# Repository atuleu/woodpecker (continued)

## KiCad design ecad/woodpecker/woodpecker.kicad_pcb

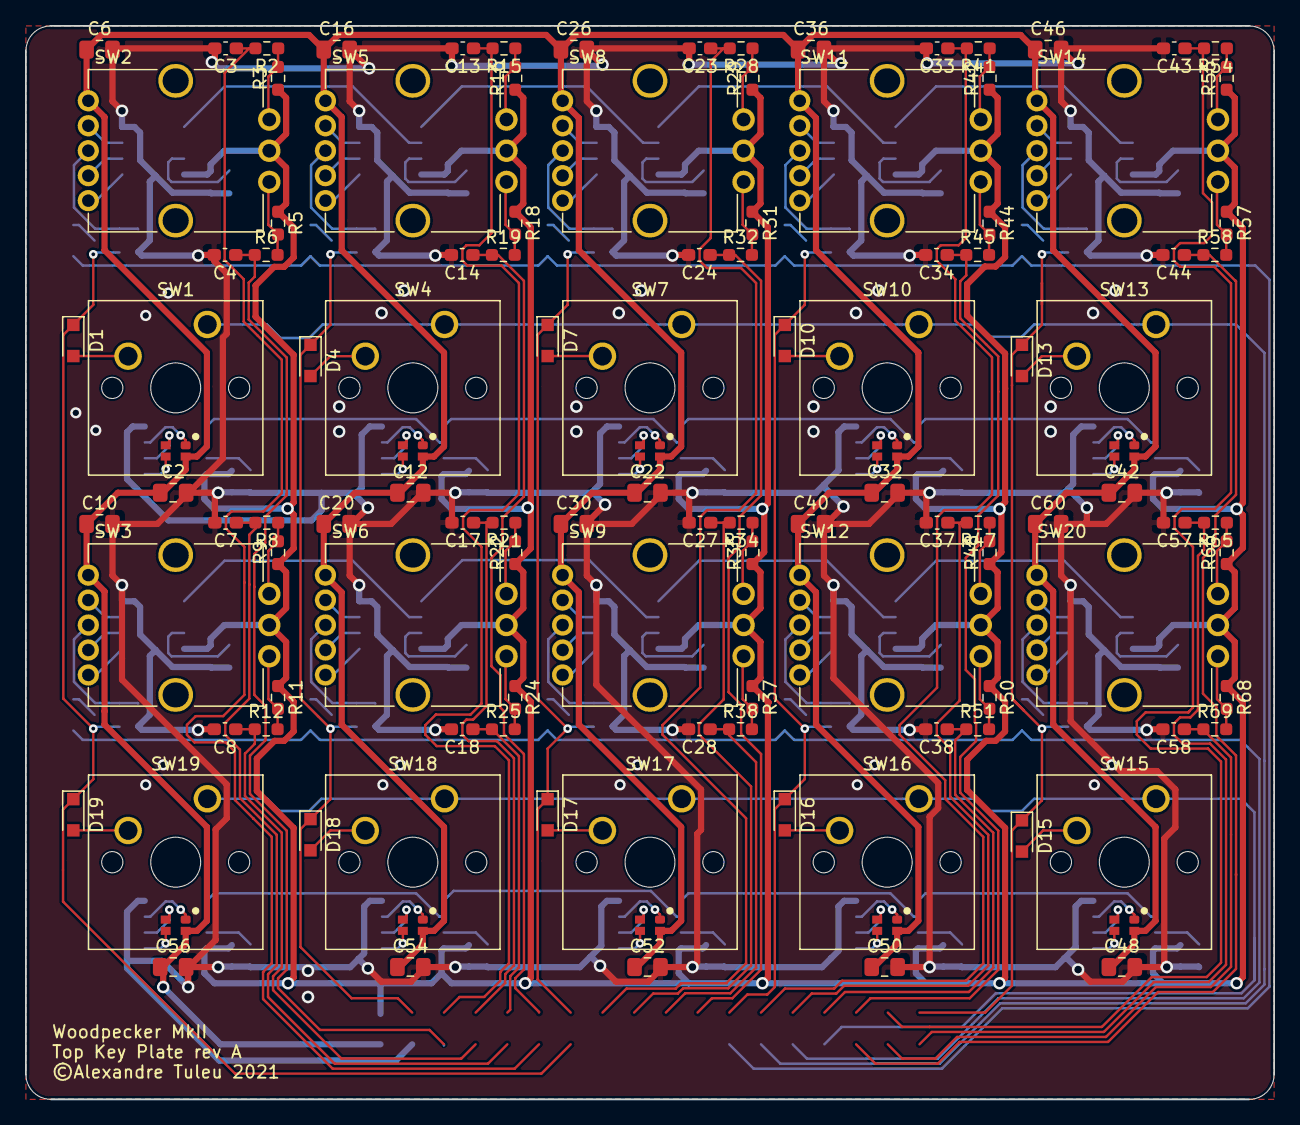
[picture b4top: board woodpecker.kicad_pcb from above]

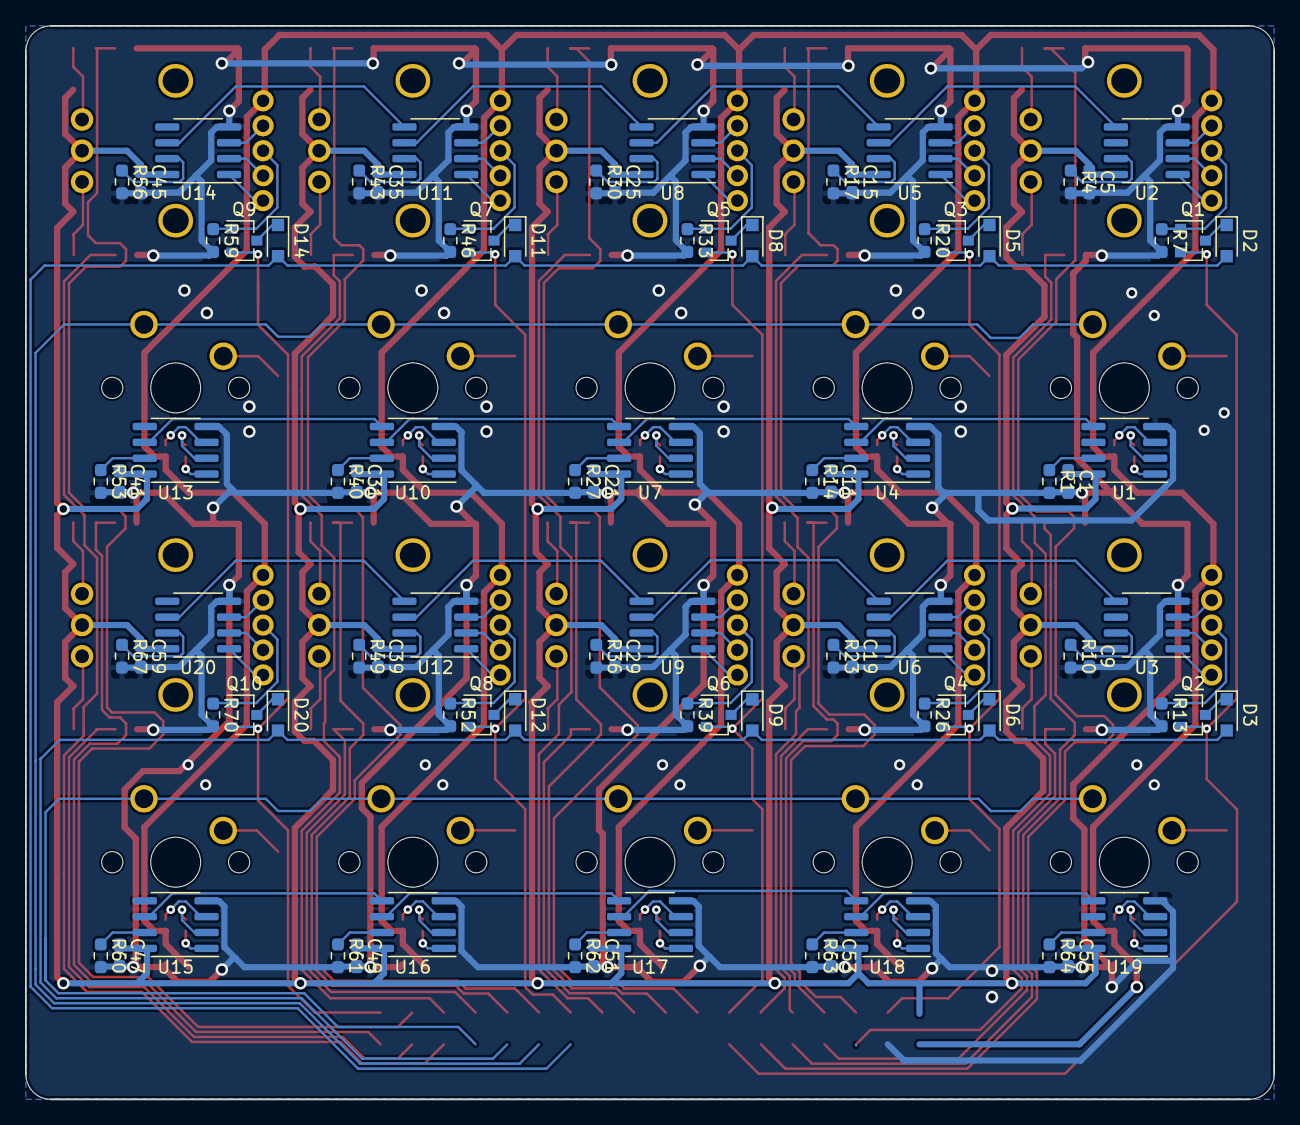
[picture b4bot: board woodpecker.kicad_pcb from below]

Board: 2 copper layers, 100.0 x 86.0 mm, 200 parts (90 on the bottom side), 178 nets.

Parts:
C1, C5, C9, C11, C15, C19, C21, C25, C29, C31, C35, C39, C41, C45, C47, C49, C51, C53, C55, C59: 100nF; C_0603_1608Metric_Pad1.08x0.95mm_HandSolder
C2, C6, C10, C12, C16, C20, C22, C26, C30, C32, C36, C40, C42, C46, C48, C50, C52, C54, C56, C60: 2.2uF; C_0805_2012Metric_Pad1.18x1.45mm_HandSolder
C3, C4, C7, C8, C13, C14, C17, C18, C23, C24, C27, C28, C33, C34, C37, C38, C43, C44, C57, C58: 10nF; C_0603_1608Metric_Pad1.08x0.95mm_HandSolder
D1, D2, D3, D4, D5, D6, D7, D8, D9, D10, D11, D12, D13, D14, D15, D16, D17, D18, D19, D20: 1N4148WS; D_SOD-323_HandSoldering
Q1, Q2, Q3, Q4, Q5, Q6, Q7, Q8, Q9, Q10: BSS138; SOT-23
R1, R4, R10, R14, R17, R23, R27, R30, R36, R40, R43, R49, R53, R56, R60, R61, R62, R63, R64, R67: 10.5K; R_0603_1608Metric_Pad0.98x0.95mm_HandSolder
R2, R3, R5, R6, R7, R8, R9, R11, R12, R13, R15, R16, R18, R19, R20, R21, R22, R24, R25, R26, R28, R29, R31, R32, R33, R34, R35, R37, R38, R39, R41, R42, R44, R45, R46, R47, R48, R50, R51, R52, R54, R55, R57, R58, R59, R65, R66, R68, R69, R70: 10K; R_0603_1608Metric_Pad0.98x0.95mm_HandSolder
SW1, SW4, SW7, SW10, SW13, SW15, SW16, SW17, SW18, SW19: Cherry_MX_LED; SW_Cherry_MX_1.00u_PCB_SMD_LED
SW2, SW3, SW5, SW6, SW8, SW9, SW11, SW12, SW14, SW20: PEL12T; PEL12T-4xxxS-S1024
U1, U2, U3, U4, U5, U6, U7, U8, U9, U10, U11, U12, U13, U14, U15, U16, U17, U18, U19, U20: TLC5973; SOIC-8_3.9x4.9mm_P1.27mm

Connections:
+3V3: C1.1, C5.1, C9.1, C11.1, C15.1, C19.1, C21.1, C25.1, C29.1, C31.1, C35.1, C39.1, C41.1, C45.1, C47.1, C49.1, C51.1, C53.1, C55.1, C59.1, R3.1, R5.1, R9.1, R11.1, R16.1, R18.1, R22.1, R24.1, R29.1, R31.1, R35.1, R37.1, R42.1, R44.1, R48.1, R50.1, R55.1, R57.1, R66.1, R68.1, SW2.C, SW3.C, SW5.C, SW6.C, SW8.C, SW9.C, SW11.C, SW12.C, SW14.C, SW20.C, U1.8, U2.8, U3.8, U4.8, U5.8, U6.8, U7.8, U8.8, U9.8, U10.8, U11.8, U12.8, U13.8, U14.8, U15.8, U16.8, U17.8, U18.8, U19.8, U20.8
/TopSection_1/COL1: D1.1, D19.1, Q1.2, Q2.2
/TopSection_1/COL2: D4.1, D18.1, Q3.2, Q4.2
/TopSection_1/COL3: D7.1, D17.1, Q5.2, Q6.2
/TopSection_1/COL4: D10.1, D16.1, Q7.2, Q8.2
/TopSection_1/COL5: D13.1, D15.1, Q9.2, Q10.2
/TopSection_1/MX_2/DI: U1.5, U4.6
/TopSection_1/MX_3/DI: U4.5, U7.6
/TopSection_1/MX_4/DI: U7.5, U10.6
/TopSection_1/MX_5/DI: U10.5, U13.6
/TopSection_1/MX_7/DI: U18.6, U19.5
/TopSection_1/MX_8/DI: U17.6, U18.5
/TopSection_1/MX_9/DI: U16.6, U17.5
/TopSection_1/MX_10/DI: U15.6, U16.5
/TopSection_1/PEL12T_2/DI: U2.5, U5.6
/TopSection_1/PEL12T_3/DI: U5.5, U8.6
/TopSection_1/PEL12T_4/DI: U8.5, U11.6
/TopSection_1/PEL12T_5/DI: U11.5, U14.6
/TopSection_1/PEL12T_7/DI: U3.5, U6.6
/TopSection_1/PEL12T_8/DI: U6.5, U9.6
/TopSection_1/PEL12T_9/DI: U9.5, U12.6
/TopSection_1/PEL12T_10/DI: U12.5, U20.6
/TopSection_1/QA1: C4.1, R6.1
/TopSection_1/QA2: C14.1, R19.1
/TopSection_1/QA3: C24.1, R32.1
/TopSection_1/QA4: C34.1, R45.1
/TopSection_1/QA5: C44.1, R58.1
/TopSection_1/QA6: C8.1, R12.1
/TopSection_1/QA7: C18.1, R25.1
/TopSection_1/QA8: C28.1, R38.1
/TopSection_1/QA9: C38.1, R51.1
/TopSection_1/QA10: C58.1, R69.1
/TopSection_1/QB1: C3.1, R2.2
/TopSection_1/QB2: C13.1, R15.2
/TopSection_1/QB3: C23.1, R28.2
/TopSection_1/QB4: C33.1, R41.2
/TopSection_1/QB5: C43.1, R54.2
/TopSection_1/QB6: C7.1, R8.2
/TopSection_1/QB7: C17.1, R21.2
/TopSection_1/QB8: C27.1, R34.2
/TopSection_1/QB9: C37.1, R47.2
/TopSection_1/QB10: C57.1, R65.2
/TopSection_1/R1: D2.2, D5.2, D8.2, D11.2, D14.2
/TopSection_1/R2: SW1.5, SW4.5, SW7.5, SW10.5, SW13.5
/TopSection_1/R3: D3.2, D6.2, D9.2, D12.2, D20.2
/TopSection_1/R4: SW15.5, SW16.5, SW17.5, SW18.5, SW19.5
GND: C1.2, C2.2, C3.2, C4.2, C5.2, C6.2, C7.2, C8.2, C9.2, C10.2, C11.2, C12.2, C13.2, C14.2, C15.2, C16.2, C17.2, C18.2, C19.2, C20.2, C21.2, C22.2, C23.2, C24.2, C25.2, C26.2, C27.2, C28.2, C29.2, C30.2, C31.2, C32.2, C33.2, C34.2, C35.2, C36.2, C37.2, C38.2, C39.2, C40.2, C41.2, C42.2, C43.2, C44.2, C45.2, C46.2, C47.2, C48.2, C49.2, C50.2, C51.2, C52.2, C53.2, C54.2, C55.2, C56.2, C57.2, C58.2, C59.2, C60.2, R1.2, R4.2, R7.2, R10.2, R13.2, R14.2, R17.2, R20.2, R23.2, R26.2, R27.2, R30.2, R33.2, R36.2, R39.2, R40.2, R43.2, R46.2, R49.2, R52.2, R53.2, R56.2, R59.2, R60.2, R61.2, R62.2, R63.2, R64.2, R67.2, R70.2, U1.4, U2.4, U3.4, U4.4, U5.4, U6.4, U7.4, U8.4, U9.4, U10.4, U11.4, U12.4, U13.4, U14.4, U15.4, U16.4, U17.4, U18.4, U19.4, U20.4
unnamed: D1.2, SW1.6
unnamed: D2.1, Q1.3
unnamed: D3.1, Q2.3
unnamed: D4.2, SW4.6
unnamed: D5.1, Q3.3
unnamed: D6.1, Q4.3
unnamed: D7.2, SW7.6
unnamed: D8.1, Q5.3
unnamed: D9.1, Q6.3
unnamed: D10.2, SW10.6
unnamed: D11.1, Q7.3
unnamed: D12.1, Q8.3
unnamed: D13.2, SW13.6
unnamed: D14.1, Q9.3
unnamed: D15.2, SW15.6
unnamed: D16.2, SW16.6
unnamed: D17.2, SW17.6
unnamed: D18.2, SW18.6
unnamed: D19.2, SW19.6
unnamed: D20.1, Q10.3
unnamed: Q1.1, R7.1, SW2.3
unnamed: Q2.1, R13.1, SW3.3
unnamed: Q3.1, R20.1, SW5.3
unnamed: Q4.1, R26.1, SW6.3
unnamed: Q5.1, R33.1, SW8.3
unnamed: Q6.1, R39.1, SW9.3
unnamed: Q7.1, R46.1, SW11.3
unnamed: Q8.1, R52.1, SW12.3
unnamed: Q9.1, R59.1, SW14.3
unnamed: Q10.1, R70.1, SW20.3
unnamed: R1.1, U1.7
unnamed: R2.1, R3.2, SW2.B
unnamed: R4.1, U2.7
unnamed: R5.2, R6.2, SW2.A
unnamed: R8.1, R9.2, SW3.B
unnamed: R10.1, U3.7
unnamed: R11.2, R12.2, SW3.A
unnamed: R14.1, U4.7
unnamed: R15.1, R16.2, SW5.B
unnamed: R17.1, U5.7
unnamed: R18.2, R19.2, SW5.A
unnamed: R21.1, R22.2, SW6.B
unnamed: R23.1, U6.7
unnamed: R24.2, R25.2, SW6.A
unnamed: R27.1, U7.7
unnamed: R28.1, R29.2, SW8.B
unnamed: R30.1, U8.7
unnamed: R31.2, R32.2, SW8.A
unnamed: R34.1, R35.2, SW9.B
unnamed: R36.1, U9.7
unnamed: R37.2, R38.2, SW9.A
unnamed: R40.1, U10.7
unnamed: R41.1, R42.2, SW11.B
unnamed: R43.1, U11.7
unnamed: R44.2, R45.2, SW11.A
unnamed: R47.1, R48.2, SW12.B
unnamed: R49.1, U12.7
unnamed: R50.2, R51.2, SW12.A
unnamed: R53.1, U13.7
unnamed: R54.1, R55.2, SW14.B
unnamed: R56.1, U14.7
unnamed: R57.2, R58.2, SW14.A
unnamed: R60.1, U15.7
unnamed: R61.1, U16.7
unnamed: R62.1, U17.7
unnamed: R63.1, U18.7
unnamed: R64.1, U19.7
unnamed: R65.1, R66.2, SW20.B
unnamed: R67.1, U20.7
unnamed: R68.2, R69.2, SW20.A
unnamed: SW1.1, U1.3
unnamed: SW1.2, U1.2
unnamed: SW1.4, U1.1
unnamed: SW2.1, U2.1
unnamed: SW2.2, U2.2
unnamed: SW2.4, U2.3
unnamed: SW3.1, U3.1
unnamed: SW3.2, U3.2
unnamed: SW3.4, U3.3
unnamed: SW4.1, U4.3
unnamed: SW4.2, U4.2
unnamed: SW4.4, U4.1
unnamed: SW5.1, U5.1
unnamed: SW5.2, U5.2
unnamed: SW5.4, U5.3
unnamed: SW6.1, U6.1
unnamed: SW6.2, U6.2
unnamed: SW6.4, U6.3
unnamed: SW7.1, U7.3
unnamed: SW7.2, U7.2
unnamed: SW7.4, U7.1
unnamed: SW8.1, U8.1
unnamed: SW8.2, U8.2
unnamed: SW8.4, U8.3
unnamed: SW9.1, U9.1
unnamed: SW9.2, U9.2
unnamed: SW9.4, U9.3
unnamed: SW10.1, U10.3
unnamed: SW10.2, U10.2
unnamed: SW10.4, U10.1
unnamed: SW11.1, U11.1
unnamed: SW11.2, U11.2
unnamed: SW11.4, U11.3
unnamed: SW12.1, U12.1
unnamed: SW12.2, U12.2
unnamed: SW12.4, U12.3
unnamed: SW13.1, U13.3
unnamed: SW13.2, U13.2
unnamed: SW13.4, U13.1
unnamed: SW14.1, U14.1
unnamed: SW14.2, U14.2
unnamed: SW14.4, U14.3
unnamed: SW15.1, U15.3
unnamed: SW15.2, U15.2
unnamed: SW15.4, U15.1
unnamed: SW16.1, U16.3
unnamed: SW16.2, U16.2
unnamed: SW16.4, U16.1
unnamed: SW17.1, U17.3
unnamed: SW17.2, U17.2
unnamed: SW17.4, U17.1
unnamed: SW18.1, U18.3
unnamed: SW18.2, U18.2
unnamed: SW18.4, U18.1
unnamed: SW19.1, U19.3
unnamed: SW19.2, U19.2
unnamed: SW19.4, U19.1
unnamed: SW20.1, U20.1
unnamed: SW20.2, U20.2
unnamed: SW20.4, U20.3
VLED: C2.1, C6.1, C10.1, C12.1, C16.1, C20.1, C22.1, C26.1, C30.1, C32.1, C36.1, C40.1, C42.1, C46.1, C48.1, C50.1, C52.1, C54.1, C56.1, C60.1, SW1.3, SW2.5, SW3.5, SW4.3, SW5.5, SW6.5, SW7.3, SW8.5, SW9.5, SW10.3, SW11.5, SW12.5, SW13.3, SW14.5, SW15.3, SW16.3, SW17.3, SW18.3, SW19.3, SW20.5
